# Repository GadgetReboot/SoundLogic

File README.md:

# SoundLogic
Sound Generator Based on 555 and Digital Logic

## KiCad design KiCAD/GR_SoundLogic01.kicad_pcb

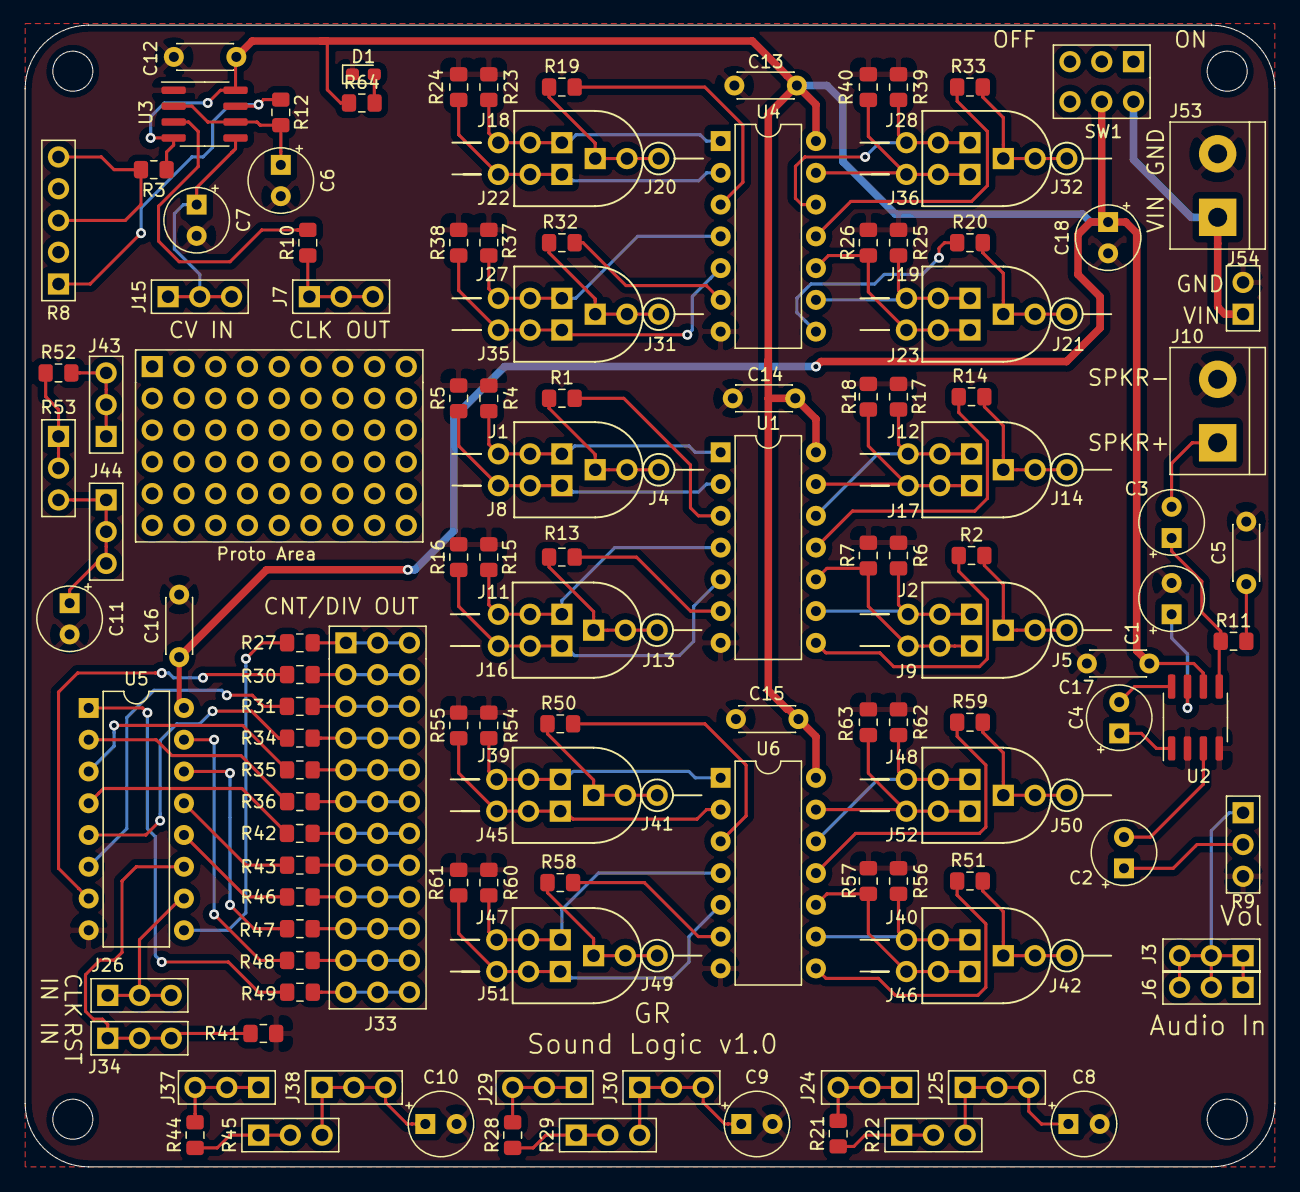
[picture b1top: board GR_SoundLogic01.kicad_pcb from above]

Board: 2 copper layers, 99.9 x 91.3 mm, 145 parts (0 on the bottom side), 105 nets.

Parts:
C1, C2, C3, C4, C6, C7, C8, C9, C10, C11, C18: 10uF; CP_Radial_Tantal_D5.0mm_P2.50mm
C5: .05uF; C_Disc_D4.3mm_W1.9mm_P5.00mm
C12, C13, C14, C15, C16, C17: 100nF; C_Disc_D4.3mm_W1.9mm_P5.00mm
D1: Power; LED_0603_1608Metric_Pad1.05x0.95mm_HandSolder
J1, J2, J4, J5, J8, J9, J11, J12, J13, J14, J16, J17, J18, J19, J20, J21, J22, J23, J27, J28, J31, J32, J35, J36, J39, J40, J41, J42, J45, J46, J47, J48, J49, J50, J51, J52: 1x3; PinHeader_1x03_P2.54mm_Vertical_NoSilk_H1.0mm
J3, J6, J7, J15, J24, J25, J26, J29, J30, J34, J37, J38, J43, J44: 1x3; PinHeader_1x03_P2.54mm_Vertical_H1.0mm
J10, J53: Screw_Terminal_01x02; TerminalBlock_bornier-2_P5.08mm
J33: Conn_01x12; PinHeader_3x12_P2.54mm_Vertical
J54: 1x2; PinHeader_1x02_P2.54mm_Vertical_H1.0mm
Proto Area: PinHeader_6x9_P2.54mm
R1, R2, R10, R13, R14, R19, R20, R27, R30, R31, R32, R33, R34, R35, R36, R42, R43, R46, R47, R48, R49, R50, R51, R58, R59: 10K; R_0805_2012Metric_Pad1.15x1.40mm_HandSolder
R3, R12, R41, R64: 4.7K; R_0805_2012Metric_Pad1.15x1.40mm_HandSolder
R4, R5, R6, R7, R15, R16, R17, R18, R23, R24, R25, R26, R37, R38, R39, R40, R54, R55, R56, R57, R60, R61, R62, R63: 1Meg; R_0805_2012Metric_Pad1.15x1.40mm_HandSolder
R8: 100K; Pot_1x05_P2.54mm_H1.0mm
R9: 10K; PinHeader_1x03_P2.54mm_Vertical_H1.0mm
R11: 10r; R_0805_2012Metric_Pad1.15x1.40mm_HandSolder
R21, R28, R44, R52: 1K; R_0805_2012Metric_Pad1.15x1.40mm_HandSolder
R22, R29, R45, R53: 100K; PinHeader_1x03_P2.54mm_Vertical_H1.0mm
SW1: SW_DPDT_x2; SlideSwitch_2x03_P2.54x3.2mm
U1, U4, U6: 74HC132; DIP-14_W7.62mm
U2: LM386; SOIC-8_3.9x4.9mm_P1.27mm
U3: 555; SOIC-8_3.9x4.9mm_P1.27mm
U5: 4040; DIP-16_W7.62mm

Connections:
GND: C1.2, C5.2, C6.2, C7.2, C8.2, C9.2, C10.2, C11.2, C12.2, C13.2, C14.2, C15.2, C16.2, C17.2, C18.2, D1.1, J10.2, J53.2, J54.2, R4.2, R5.2, R6.2, R7.2, R9.3, R15.2, R16.2, R17.2, R18.2, R23.2, R24.2, R25.2, R26.2, R37.2, R38.2, R39.2, R40.2, R41.2, R54.2, R55.2, R56.2, R57.2, R60.2, R61.2, R62.2, R63.2, U1.7, U2.2, U2.4, U3.1, U4.7, U5.8, U6.7
unnamed: C1.1, U2.7
unnamed: C2.1, R9.2
unnamed: C2.2, U2.3
unnamed: C3.1, R11.1, U2.5
unnamed: C3.2, J10.1
unnamed: C4.1, U2.1
unnamed: C4.2, U2.8
unnamed: C5.1, R11.2
unnamed: C6.1, R12.2, U3.2, U3.6
unnamed: C7.1, J15.1, J15.2, J15.3, U3.5
unnamed: C8.1, J25.1, J25.2, J25.3, R22.3
unnamed: C9.1, J30.1, J30.2, J30.3, R29.3
unnamed: C10.1, J38.1, J38.2, J38.3, R45.3
unnamed: C11.1, J44.1, J44.2, J44.3, R53.3
unnamed: D1.2, R64.2
unnamed: J1.1, J1.2, J1.3, R4.1, U1.1
unnamed: J2.1, J2.2, J2.3, R6.1, U1.9
unnamed: J3.1, J3.2, J3.3, J6.1, J6.2, J6.3, R9.1
unnamed: J4.1, J4.2, J4.3, R1.1
unnamed: J5.1, J5.2, J5.3, R2.1
unnamed: J7.1, J7.2, J7.3, R10.1
unnamed: J8.1, J8.2, J8.3, R5.1, U1.2
unnamed: J9.1, J9.2, J9.3, R7.1, U1.10
unnamed: J11.1, J11.2, J11.3, R15.1, U1.4
unnamed: J12.1, J12.2, J12.3, R17.1, U1.12
unnamed: J13.1, J13.2, J13.3, R13.1
unnamed: J14.1, J14.2, J14.3, R14.1
unnamed: J16.1, J16.2, J16.3, R16.1, U1.5
unnamed: J17.1, J17.2, J17.3, R18.1, U1.13
unnamed: J18.1, J18.2, J18.3, R23.1, U4.1
unnamed: J19.1, J19.2, J19.3, R25.1, U4.9
unnamed: J20.1, J20.2, J20.3, R19.1
unnamed: J21.1, J21.2, J21.3, R20.1
unnamed: J22.1, J22.2, J22.3, R24.1, U4.2
unnamed: J23.1, J23.2, J23.3, R26.1, U4.10
unnamed: J24.1, J24.2, J24.3, R21.2
unnamed: J26.1, J26.2, J26.3, U5.10
unnamed: J27.1, J27.2, J27.3, R37.1, U4.4
unnamed: J28.1, J28.2, J28.3, R39.1, U4.12
unnamed: J29.1, J29.2, J29.3, R28.2
unnamed: J31.1, J31.2, J31.3, R32.1
unnamed: J32.1, J32.2, J32.3, R33.1
unnamed: J33.1, R27.1
unnamed: J33.2, R30.1
unnamed: J33.3, R31.1
unnamed: J33.4, R34.1
unnamed: J33.5, R35.1
unnamed: J33.6, R36.1
unnamed: J33.7, R42.1
unnamed: J33.8, R43.1
unnamed: J33.9, R46.1
unnamed: J33.10, R47.1
unnamed: J33.11, R48.1
unnamed: J33.12, R49.1
unnamed: J34.1, J34.2, J34.3, R41.1, U5.11
unnamed: J35.1, J35.2, J35.3, R38.1, U4.5
unnamed: J36.1, J36.2, J36.3, R40.1, U4.13
unnamed: J37.1, J37.2, J37.3, R44.2
unnamed: J39.1, J39.2, J39.3, R54.1, U6.1
unnamed: J40.1, J40.2, J40.3, R56.1, U6.9
unnamed: J41.1, J41.2, J41.3, R50.1
unnamed: J42.1, J42.2, J42.3, R51.1
unnamed: J43.1, J43.2, J43.3, R52.2
unnamed: J45.1, J45.2, J45.3, R55.1, U6.2
unnamed: J46.1, J46.2, J46.3, R57.1, U6.10
unnamed: J47.1, J47.2, J47.3, R60.1, U6.4
unnamed: J48.1, J48.2, J48.3, R62.1, U6.12
unnamed: J49.1, J49.2, J49.3, R58.1
unnamed: J50.1, J50.2, J50.3, R59.1
unnamed: J51.1, J51.2, J51.3, R61.1, U6.5
unnamed: J52.1, J52.2, J52.3, R63.1, U6.13
unnamed: J53.1, J54.1, SW1.4
unnamed: R1.2, U1.3
unnamed: R2.2, U1.8
unnamed: R3.2, R8.2, R8.3
unnamed: R10.2, U3.3
unnamed: R8.1, R12.1, U3.7
unnamed: R13.2, U1.6
unnamed: R14.2, U1.11
unnamed: R19.2, U4.3
unnamed: R20.2, U4.8
unnamed: R21.1, R22.1, R22.2
unnamed: R27.2, U5.9
unnamed: R28.1, R29.1, R29.2
unnamed: R30.2, U5.7
unnamed: R31.2, U5.6
unnamed: R32.2, U4.6
unnamed: R33.2, U4.11
unnamed: R34.2, U5.5
unnamed: R35.2, U5.3
unnamed: R36.2, U5.2
unnamed: R42.2, U5.4
unnamed: R43.2, U5.13
unnamed: R44.1, R45.1, R45.2
unnamed: R46.2, U5.12
unnamed: R47.2, U5.14
unnamed: R48.2, U5.15
unnamed: R49.2, U5.1
unnamed: R50.2, U6.3
unnamed: R51.2, U6.8
unnamed: R52.1, R53.1, R53.2
unnamed: R58.2, U6.6
unnamed: R59.2, U6.11
VCC: C12.1, C13.1, C14.1, C15.1, C16.1, C17.1, C18.1, R3.1, R64.1, SW1.5, U1.14, U2.6, U3.4, U3.8, U4.14, U5.16, U6.14

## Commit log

2019-10-04 Create readme.md
    PCB Gerber files
